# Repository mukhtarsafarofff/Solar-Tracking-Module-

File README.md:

(ENG) This solar tracker is  a system that positions an object at an angle relative to the Sun. Here i have used LDR to detect the presence of light / measuring the intensity of light. In This circuit  I can  adjust the threshold (sensitivity) of digital output by tuning the on-board variable resistor (potentiometer).  Simple usage as it is the digital output, so you will know is the light present and decide what to do with it. L293D  IC is a medium power motor driver perfect for driving DC Motors and this driver  greatly simplifies and increases the ease with which you may control motors, relays, etc from micro-controllers.   It can drive motors up to 12V with a total DC current of up to 600mA.When LDR2 receives more light than LDR1, it offers lower resistance than LDR1, providing a high input to comparators A1 and A2 at pins 4 and 7, respectively. As a result, output pin 1 of comparator A2 goes high to rotate motor M1 in one direction (say, anti-clockwise) and turn the solar panel.  When LDR1 receives more light than LDR2, it offers lower resistance than LDR2, giving a low input to comparators A1 and A2 at pins 4 and 7, respectively.  As the voltage at pin 5 of comparator A1 is now higher than the voltage at its pin 4, its output pin 2 goes high. As a result, motor M1 rotates in the opposite direction (say, clock-wise) and the solar panel turns.Similarly, LDR3 and LDR4 track the sun along Y axis.

(DEU) Dieser Solartracker ist ein System, das ein Objekt relativ zur Sonne ausrichtet. Hier habe ich LDR verwendet, um die Anwesenheit von Licht zu erkennen bzw. die Lichtintensität zu messen. In diesem Schaltkreis kann ich die Schwelle (Empfindlichkeit) des digitalen Ausgangs durch Justieren des an Bord befindlichen variablen Widerstands (Potentiometer) einstellen. Die Verwendung ist einfach, da es sich um einen digitalen Ausgang handelt, sodass Sie erkennen können, ob Licht vorhanden ist und entscheiden können, was damit zu tun ist. Der L293D IC ist ein mittelstarker Motortreiber, der perfekt für das Ansteuern von Gleichstrommotoren geeignet ist, und dieser Treiber vereinfacht und erhöht die Benutzerfreundlichkeit, mit der Sie Motoren, Relais usw. von Mikrocontrollern aus steuern können. Er kann Motoren bis zu 12V mit einem gesamten Gleichstrom von bis zu 600mA antreiben. Wenn LDR2 mehr Licht als LDR1 empfängt, bietet er einen geringeren Widerstand als LDR1 und liefert einen hohen Eingang an die Komparatoren A1 und A2 an den Pins 4 und 7.  Infolgedessen geht der Ausgangspin 1 des Komparators A2 hoch, um den Motor M1 in eine Richtung (sagen wir, gegen den Uhrzeigersinn) zu drehen und das Solarpanel zu bewegen. Wenn LDR1 mehr Licht als LDR2 empfängt, bietet es einen geringeren Widerstand als LDR2, was zu einem niedrigen Eingang an die Komparatoren A1 und A2 an den Pins 4 und 7 führt.  Da die Spannung am Pin 5 von Komparator A1 jetzt höher ist als die Spannung an seinem Pin 4,  geht sein Ausgangspin 2 hoch.  Infolgedessen dreht sich Motor M1 in die entgegengesetzte Richtung (sagen wir, im Uhrzeigersinn) und das Solarpanel dreht sich.  Ähnlich verfolgen LDR3 und LDR4 die Sonne entlang der Y-Achse.

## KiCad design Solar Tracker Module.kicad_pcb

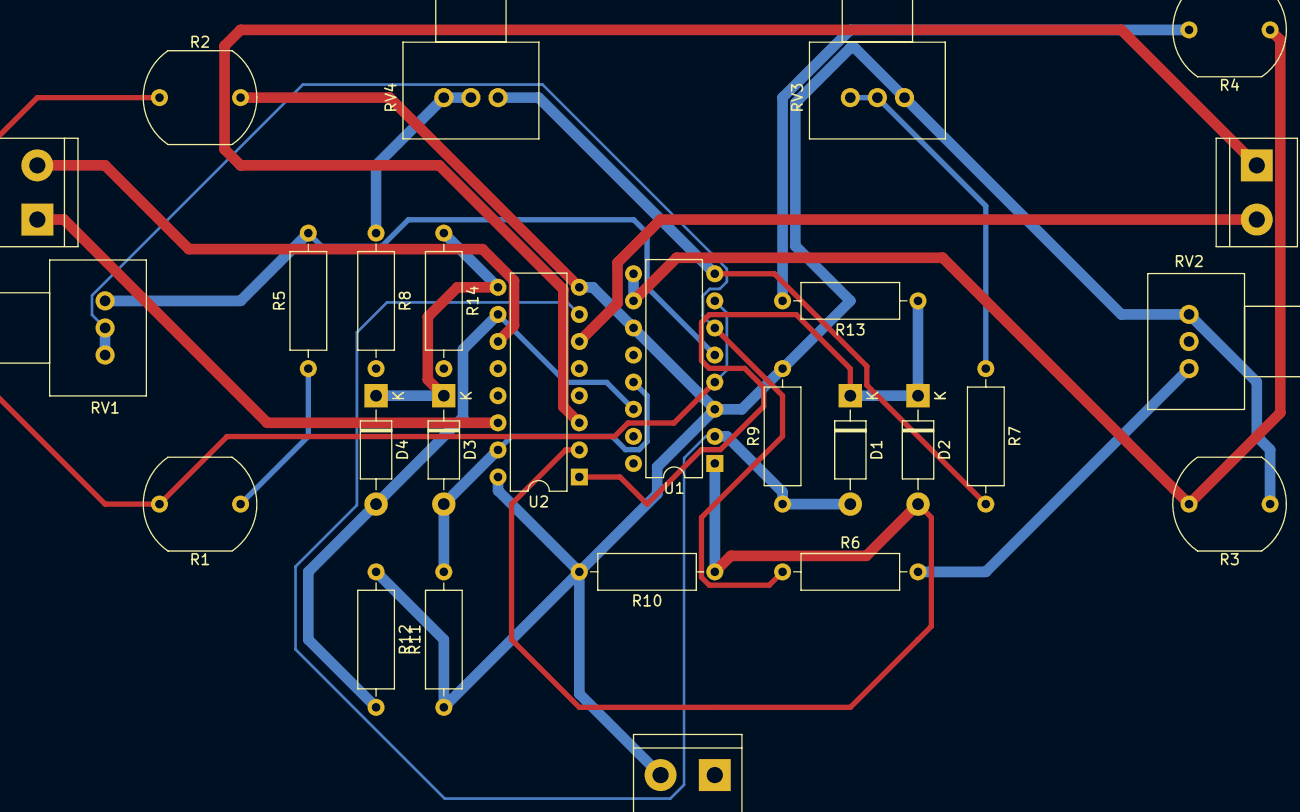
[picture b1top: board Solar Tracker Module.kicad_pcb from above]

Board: 2 copper layers, 27 parts (0 on the bottom side), 21 nets.

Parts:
D1, D2, D3, D4: 1N4007; D_DO-41_SOD81_P10.16mm_Horizontal
J1: Screw_Terminal_01x02; TerminalBlock_bornier-2_P5.08mm
M1, M2: Motor_DC; TerminalBlock_bornier-2_P5.08mm
R1: LDR1; R_LDR_10x8.5mm_P7.6mm_Vertical
R2: LDR2; R_LDR_10x8.5mm_P7.6mm_Vertical
R3: LDR3; R_LDR_10x8.5mm_P7.6mm_Vertical
R4: LDR4; R_LDR_10x8.5mm_P7.6mm_Vertical
R5: 50K; R_Axial_DIN0309_L9.0mm_D3.2mm_P12.70mm_Horizontal
R6: 12K; R_Axial_DIN0309_L9.0mm_D3.2mm_P12.70mm_Horizontal
R7: 12k; R_Axial_DIN0309_L9.0mm_D3.2mm_P12.70mm_Horizontal
R8: 50k; R_Axial_DIN0309_L9.0mm_D3.2mm_P12.70mm_Horizontal
R9, R10, R11, R12: 10K; R_Axial_DIN0309_L9.0mm_D3.2mm_P12.70mm_Horizontal
R13, R14: 22K; R_Axial_DIN0309_L9.0mm_D3.2mm_P12.70mm_Horizontal
RV1, RV4: 47K; Potentiometer_Vishay_148-149_Single_Horizontal
RV2, RV3: 100K; Potentiometer_Vishay_148-149_Single_Horizontal
U1: LM339; DIP-16_W7.62mm
U2: L293D; DIP-16_W7.62mm

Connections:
1: D1.1 (K), D2.1 (K), R13.1, U2.1 (EN1,2)
7: D1.2 (A), R9.1, U1.2, U2.7 (2A)
10: D4.2 (A), R12.2, U1.14, U2.10 (3A)
15: D3.2 (A), R11.2, U1.13, U2.15 (4A)
+12V: J1.2, R2.2, R3.1, R9.2, R10.2, R11.1, R12.1, RV2.3, RV3.1, U1.3 (V+), U1.11 (+), U2.8 (VCC2), U2.16 (VCC1)
Earth: J1.1, R4.2, R8.2, R13.2, R14.2, U1.12 (V-), U2.4 (GND), U2.5 (GND), U2.12 (GND), U2.13 (GND)
unnamed: D2.2 (A), R10.1, U1.1, U2.2 (1A)
unnamed: D3.1 (K), D4.1 (K), R14.1, U2.9 (EN3,4)
unnamed: M1.1 (+), U2.3 (1Y)
unnamed: M1.2 (-), U2.6 (2Y)
unnamed: M2.1 (+), U2.14 (4Y)
unnamed: M2.2 (-), U2.11 (3Y)
unnamed: R1.1, R5.1
unnamed: R6.2, RV2.1, RV2.2
unnamed: R7.1, RV3.2, RV3.3
unnamed: R8.1, RV4.2, RV4.3
unnamed: R5.2, RV1.1, U1.5 (+)
unnamed: R1.2, R2.1, U1.4 (-), U1.7 (+)
unnamed: R6.1, RV1.2, RV1.3, U1.6 (-)
unnamed: R3.2, R4.1, U1.9 (+), U1.10 (-)
unnamed: R7.2, RV4.1, U1.8 (-)

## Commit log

2024-04-03 Solar Tracking Module is accomplished
